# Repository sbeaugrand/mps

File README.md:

# Build
```sh
make help  # :
```
```sh
docker build -t debian13-armhf-base -f makefiles/Dockerfile.armhf .
docker build -t debian13-arm64-base -f makefiles/Dockerfile.arm64 .
docker build -t debian13-armhf -f Dockerfile.armhf .
docker build -t debian13-arm64 -f Dockerfile.arm64 .
make docker-xc XC=arm-linux-gnueabihf
make docker-xp XC=arm-linux-gnueabihf
make docker-xc XC=aarch64-linux-gnu
make docker-xp XC=aarch64-linux-gnu
```

# Structure of album directories
`music_directory/additional_directory/artist - year - album/00.m3u`

`music_directory` :
from /etc/mpd.conf

`additional_directory` :
to use weights in random selection of albums,
weights will be in music_directory/mps.weights

# [Client state diagram](README-0.md)
```mermaid
stateDiagram
    direction LR
    [*] --> Normal
    Normal --> Normal: setup / ok / up / down / right
    Normal --> Album: left
    Album --> Normal: ok / setup
    Album --> Album: up / down
    Album --> Artist: left
    Artist --> Album: setup
    Artist --> Artist: letter
```

# [Screensaver state diagram](README-0.md)
```mermaid
stateDiagram
    direction LR
    [*] --> Normal
    Normal --> Menu: ok
    Menu --> Normal: ok = cancel
    Menu --> Normal: right = /usr/bin/rtc
    Menu --> [*]: up = reboot / down = halt
    Menu --> Date: left
    Date --> Date: dir
    Date --> Hour: ok
    Hour --> Hour: dir
    Hour --> Menu: ok
```

# [Main sequence diagram](README-0.md)
```mermaid
sequenceDiagram
    Participant U as User
    Participant C as Client
    Participant S as Server
    loop
        U->>C: event "setup"
        activate C
        C->>+S: call "rand"
        S-->>-C: album
        deactivate C
    end
    Note over U,S: Less than 20 seconds
    U->>C: event "ok"
    activate C
    C->>+S: call "ok"
    S-->>-C: album
    C->>+S: call "checksum"
    S-->>-C: album
    deactivate C
```

# Divers

<details>
  <summary>Test without arm</summary>

  ```console
  terminal1> make build
  terminal1> make server
  terminal2> make client  # KEY_SETUP, KEY_OK, ...
  terminal3> make dir path=
  terminal3> ./client.py
  terminal3> ./client.py [method]  # rand, ok, ...
  terminal3> ./client.py quit
  ```
</details>

<details>
  <summary>php usage</summary>

  ```console
  terminal1> make tunnel
  terminal2> make php
  ```
</details>

<details>
  <summary>music_directory update</summary>

  ```sh
  mpc update
  rm mps.list
  sudo systemctl restart mpserver
  ```
</details>

<details>
  <summary>manpages update</summary>

  ```sh
  make
  cp build/*.1 .
  ```
</details>

<details>
  <summary>No apt list update</summary>

  ```sh
  sudo mv /etc/apt/apt.conf.d/02-armbian-postupdate ~/
  ```
</details>

<details>
  <summary>mpc usage for debug</summary>

  ```sh
  mpc clear
  mpc load '<[inside_music_directory]>/00.m3u'
  mpc play
  ```
</details>

<details>
  <summary>Comparison between jsonrpccpp and json-rpc-cxx</summary>

https://github.com/sbeaugrand/debinst/tree/master/cicd/mps

json-rpc-cxx:
- compile time x2
- binary size x3
</details>

# BOM 2021
[pdf](http://beaugrand.chez.com/pdf/remoteControl.pdf)

# BOM 2025
|Article|TTC|Nombre|Total|
|-------------------------------------------------------------------------------------------------------------|-----:|:-----:|-----:|
|[Platine sans cuivre 100x160mm](https://www.conrad.fr/fr/search.html?search=529569)                          |  3.99|1      |  3.99|
|[Connecteur femelle pour CI 32 contacts](https://fr.rs-online.com/web/p/connecteurs-femelles-pour-ci/1803928)| 19.00|39/32/5|  4.63|
|[Barrette mâle 40 pôles 12.50](https://www.conrad.fr/fr/search.html?search=1390110)                          |  3.80|1/5    |  0.76|
|[Barrette femelle 20 pôles coudée](https://www.conrad.fr/fr/search.html?search=1560681)                      |  3.99|15/20  |  2.99|
|[Barrette femelle 36 pôles droite](https://www.conrad.fr/fr/search.html?search=1560794)                      |  4.29|22/36  |  2.62|
|[Connecteur USB mâle coudé](https://www.conrad.fr/fr/search.html?search=1567163)                             |  3.29|1      |  3.29|
|[Connecteur USB femelle coudé](https://www.conrad.fr/fr/search.html?search=1567164)                          |  3.29|1      |  3.29|
|[Entretoise M3 25mm acier galvanisé](https://www.conrad.fr/fr/search.html?search=521678)                     |  2.99|4/10   |  1.20|
|[Entretoise M3 15mm Polyamide](https://www.conrad.fr/fr/search.html?search=2163259)                          |  3.08|2/7    |  0.88|
|[Vis M3 6mm Polyamide](https://www.conrad.fr/fr/search.html?search=1817006)                                  |  9.99|8/200  |  0.40|
|[Module RTC](https://www.conrad.fr/fr/search.html?search=2481842)                                            |  9.99|1/2    |  5.00|
|[Récepteur infrarouge 1838](https://www.conrad.fr/fr/search.html?search=1572283)                             |  1.79|1/2    |  0.90|
|[Télécommande IRC01](https://www.gotronic.fr/art-telecommande-ir-irc01-19568.htm)                            |  2.90|1      |  2.90|
|[Embase d'alimentation 2.1mm 5.5mm](https://www.conrad.fr/fr/search.html?search=735754)                      |  1.84|1/2    |  0.92|
|[Bloc d'alimentation 12V 1A](https://www.conrad.fr/fr/search.html?search=3397133)                            | 10.99|1      | 10.99|
|[Carte SD A1](https://fr.rs-online.com/web/p/cartes-sd/2836581)                                              | 11.68|1      | 11.68|
|[Condensateur 1000uF 16V 10x16mm](https://www.conrad.fr/fr/search.html?search=443933)                        |  4.00|2/20   |  0.40|
|[Interrupteur à levier 2 x On/On](https://www.conrad.fr/fr/search.html?search=1589399)                       |  1.99|2      |  3.98|
|[Patte d'assemblage 100x15x2mm](https://www.bricorama.fr/search?q=3274590517126)                             |  1.10|3      |  3.30|
|[Patte d'assemblage 60x15x2mm](https://www.bricorama.fr/search?q=3274590517102)                              |  1.10|4      |  4.40|
|[Charnière 40x25mm entraxe 27mm](https://www.bricorama.fr/search?q=3505391042136)                            |  5.40|1/2    |  2.70|
|[NanoPi NEO-LTS soldered](https://fr.aliexpress.com/item/1005005383857521.html)                              | 21.55|1      | 21.55|
|[Ampli XH-M567 TPA3116D2](https://fr.aliexpress.com/item/1005004830515523.html)                              |  3.39|1      |  3.39|
|[Régulateur de tension LM2596](https://fr.aliexpress.com/item/1005005970782265.html)                         |  1.32|1      |  1.32|
|[OLED blanc 1.3 i2c gnd](https://fr.aliexpress.com/item/1005006862867338.html)                               |  2.42|1      |  2.42|
|==Total==                                                                                                    |146.66|       | 99.89|
|**Alternative**|**TTC**|**Nombre**|**Total**|
|[NanoPi NEO2](https://fr.aliexpress.com/item/1005008828046430.html)                                          | 38.88|1      | 38.88|
|[Connecteur femelle pour CI 36 contacts](https://fr.rs-online.com/web/p/connecteurs-femelles-pour-ci/5490026)| 34.23|8/36/5 |  1.52|
|[Entretoise filetée 15mm](https://fr.rs-online.com/web/p/entretoises-filetees/1026378)                       |  6.43|4/10   |  2.57|
|[Vis à tête Cylindrique Cruciforme M3 8mm](https://fr.rs-online.com/web/p/vis-a-metaux/1854437)              |  5.02|8/20   |  2.01|

# License CeCILL 2.1

Copyright Sébastien Beaugrand

This software is governed by the CeCILL license under French law and
abiding by the rules of distribution of free software. You can use,
modify and/or redistribute the software under the terms of the CeCILL
license as circulated by CEA, CNRS and INRIA at the following URL
"http://www.cecill.info".

As a counterpart to the access to the source code and rights to copy,
modify and redistribute granted by the license, users are provided only
with a limited warranty and the software's author, the holder of the
economic rights, and the successive licensors have only limited
liability.

In this respect, the user's attention is drawn to the risks associated
with loading, using, modifying and/or developing or reproducing the
software by the user in light of its specific status of free software,
that may mean that it is complicated to manipulate, and that also
therefore means that it is reserved for developers and experienced
professionals having in-depth computer knowledge. Users are therefore
encouraged to load and test the software's suitability as regards their
requirements in conditions enabling the security of their systems and/or
data to be ensured and, more generally, to use and operate it in the
same conditions as regards security.

The fact that you are presently reading this means that you have had
knowledge of the CeCILL license and that you accept its terms.

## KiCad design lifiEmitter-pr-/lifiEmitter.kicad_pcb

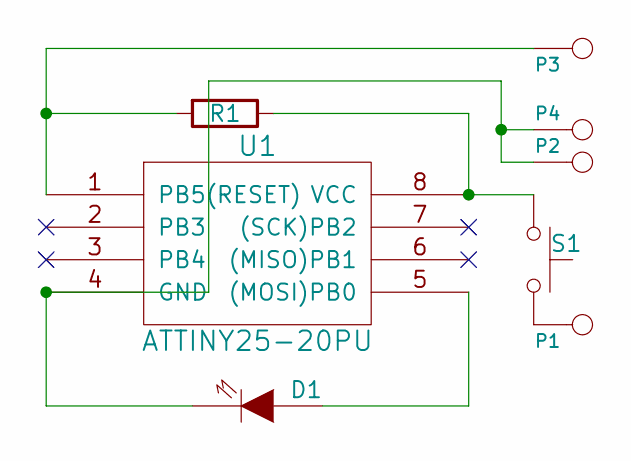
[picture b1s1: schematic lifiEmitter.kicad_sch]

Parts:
D1: LED; LED-5MM
P1, P2, P3, P4: CONN_1; PIN_ARRAY_1X1
R1: R; R4
S1: SW_Push; SW_PUSH_SMALL
U1: ATTINY25-20PU; DIP-8__300

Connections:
unnamed: D1.1 (A), U1.5 ((MOSI)PB0)
unnamed: D1.2 (K), P2.1, P4.1, U1.4 (GND)
unnamed: P1.1, S1.2
unnamed: P3.1, R1.2, U1.1 (PB5(RESET))
unnamed: R1.1, S1.1, U1.8 (VCC)

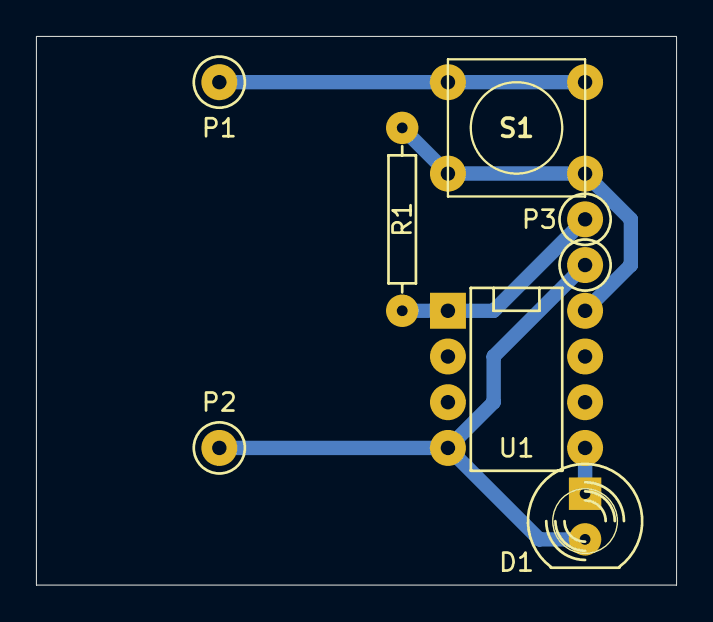
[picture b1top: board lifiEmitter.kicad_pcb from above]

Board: 2 copper layers, 35.6 x 30.5 mm, 8 parts (0 on the bottom side), 5 nets.

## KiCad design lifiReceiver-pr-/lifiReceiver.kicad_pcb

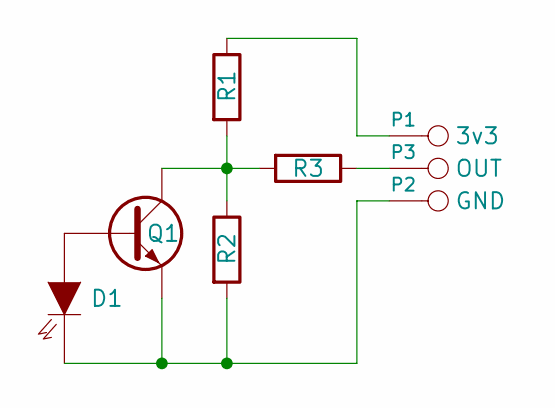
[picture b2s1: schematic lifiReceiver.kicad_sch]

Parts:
D1: LED; LED-5MM
P1, P2, P3: CONN_1; PIN_ARRAY_1X1
Q1: NPN
R1, R2, R3: R; R4

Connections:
unnamed: D1.1 (A), Q1.2 (B)
unnamed: D1.2 (K), P2.1, Q1.3 (E), R2.2
unnamed: P1.1, R1.1
unnamed: P3.1, R3.1
unnamed: Q1.1 (C), R1.2, R2.1, R3.2

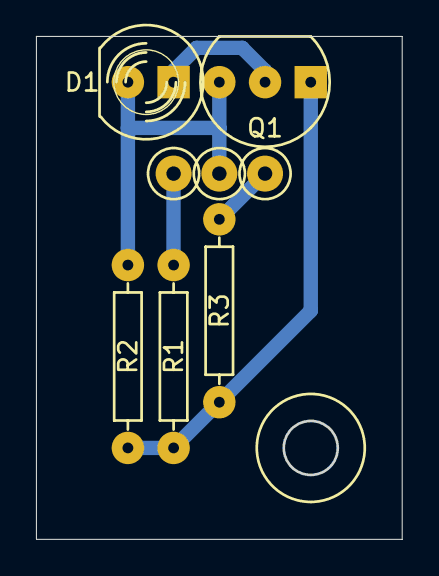
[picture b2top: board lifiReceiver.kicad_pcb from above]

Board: 2 copper layers, 20.3 x 27.9 mm, 8 parts (0 on the bottom side), 5 nets.
